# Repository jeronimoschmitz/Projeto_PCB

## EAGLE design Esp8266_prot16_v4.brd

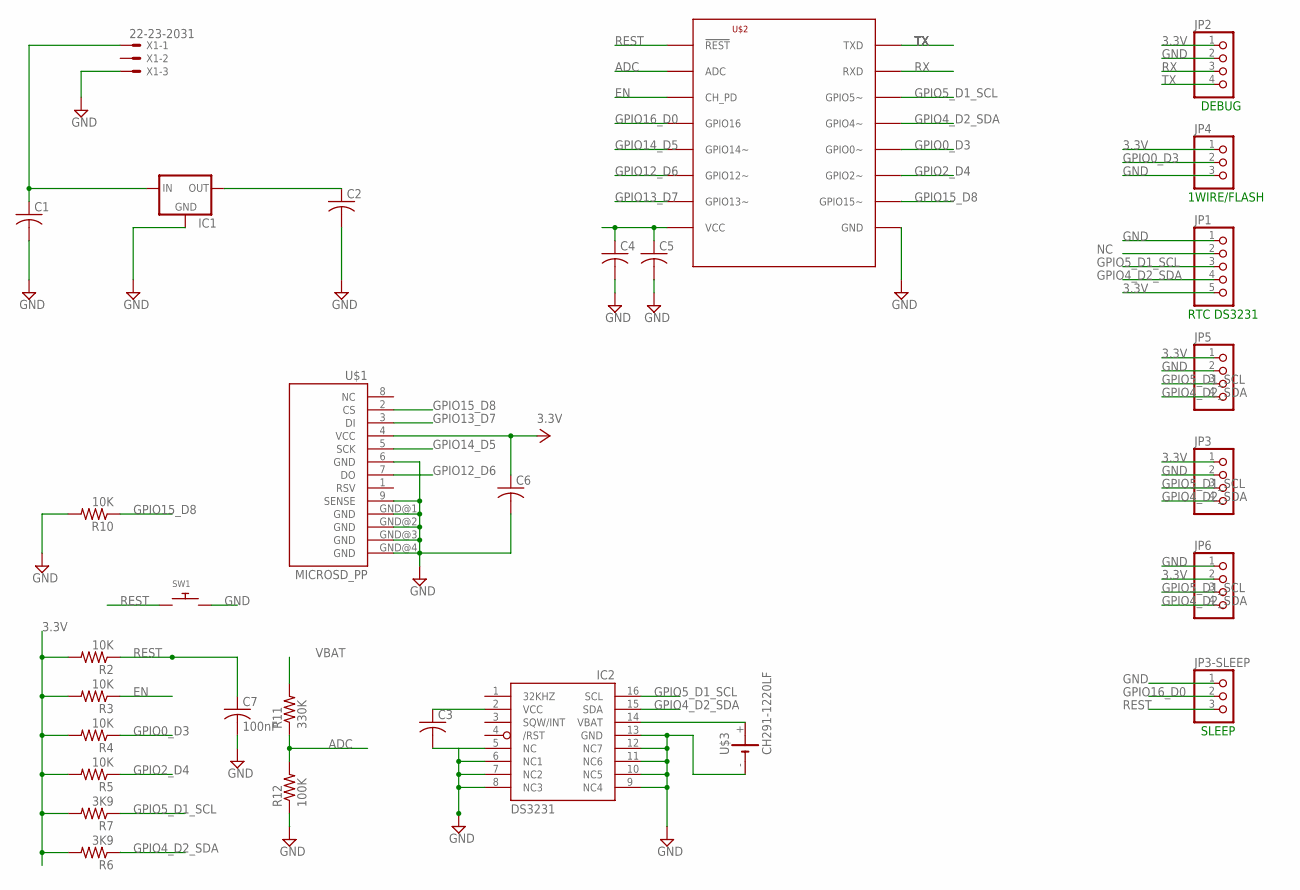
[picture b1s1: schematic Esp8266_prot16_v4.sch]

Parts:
C1, C2, C3, C4, C5, C6: C-USC0805K; C0805K
C7: 100nF; C0805K
IC1: XC63FPP; SOT89R
IC2: DS3231/SO; SO16W
JP1: PINHD-1X5/90; 1X05/90
JP2, JP5, JP6: PINHD-1X4; 1X04
JP3: PINHD-1X4/90; 1X04/90
JP3-SLEEP: PINHD-1X3/90; 1X03/90
JP4: PINHD-1X3; 1X03
R2, R3, R4, R5, R10: 10K; R0805
R6, R7: 3K9; R0805
R11: 330K; R0805
R12: 100K; R0805
SW1: SWITCH_PUSHBUTTONEVQ-PE; TACT_PANA-EVQ
U$1: MICROSD_PP
U$2: ESP8266-07; ESP-07
U$3: CH291-1220LF
X1: 22-23-2031

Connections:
3.3V: C2.1, C3.1, C4.1, C5.1, C6.1, IC1.3 (OUT), IC2.2 (VCC), JP1.5, JP2.1, JP3.1, JP4.1, JP5.1, JP6.2, R2.2, R3.2, R4.2, R5.2, R6.2, R7.2, U$1.4 (VCC), U$2.VCC
ADC: R11.1, R12.2, U$2.ADC
BATRTC: IC2.14 (VBAT), U$3.+
EN: R3.1, U$2.CH_PD
GND: C1.2, C2.2, C3.2, C4.2, C5.2, C6.2, C7.2, IC1.1 (GND), IC2.5 (NC), IC2.6 (NC1), IC2.7 (NC2), IC2.8 (NC3), IC2.9 (NC4), IC2.10 (NC5), IC2.11 (NC6), IC2.12 (NC7), IC2.13 (GND), JP1.1, JP2.2, JP3.2, JP3-SLEEP.1, JP4.3, JP5.2, JP6.1, R10.2, R12.1, SW1.P$2, U$1.6 (GND), U$1.9 (SENSE), U$1.GND@1 (GND), U$1.GND@2 (GND), U$1.GND@3 (GND), U$1.GND@4 (GND), U$2.GND, U$3.-, X1.3
GPIO0_D3: JP4.2, R4.1, U$2.GPIO0 (GPIO0~)
GPIO2_D4: R5.1, U$2.GPIO2 (GPIO2~)
GPIO4_D2_SDA: IC2.15 (SDA), JP1.4, JP3.4, JP5.4, JP6.4, R6.1, U$2.GPIO5 (GPIO4~)
GPIO5_D1_SCL: IC2.16 (SCL), JP1.3, JP3.3, JP5.3, JP6.3, R7.1, U$2.GPIO4 (GPIO5~)
GPIO12_D6: U$1.7 (DO), U$2.GPIO12 (GPIO12~)
GPIO13_D7: U$1.3 (DI), U$2.GPIO13 (GPIO13~)
GPIO14_D5: U$1.5 (SCK), U$2.GPIO14 (GPIO14~)
GPIO15_D8: R10.1, U$1.2 (CS), U$2.GPIO15 (GPIO15~)
GPIO16_D0: JP3-SLEEP.2, U$2.GPIO16
NC: JP1.2
REST: C7.1, JP3-SLEEP.3, R2.1, SW1.P$1, U$2.REST (!REST)
RX: JP2.3, U$2.RXD
TX: JP2.4, U$2.TXD
VBAT: C1.1, IC1.2 (IN), R11.2, X1.1

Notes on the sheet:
RTC DS3231
1WIRE/FLASH
DEBUG
SLEEP

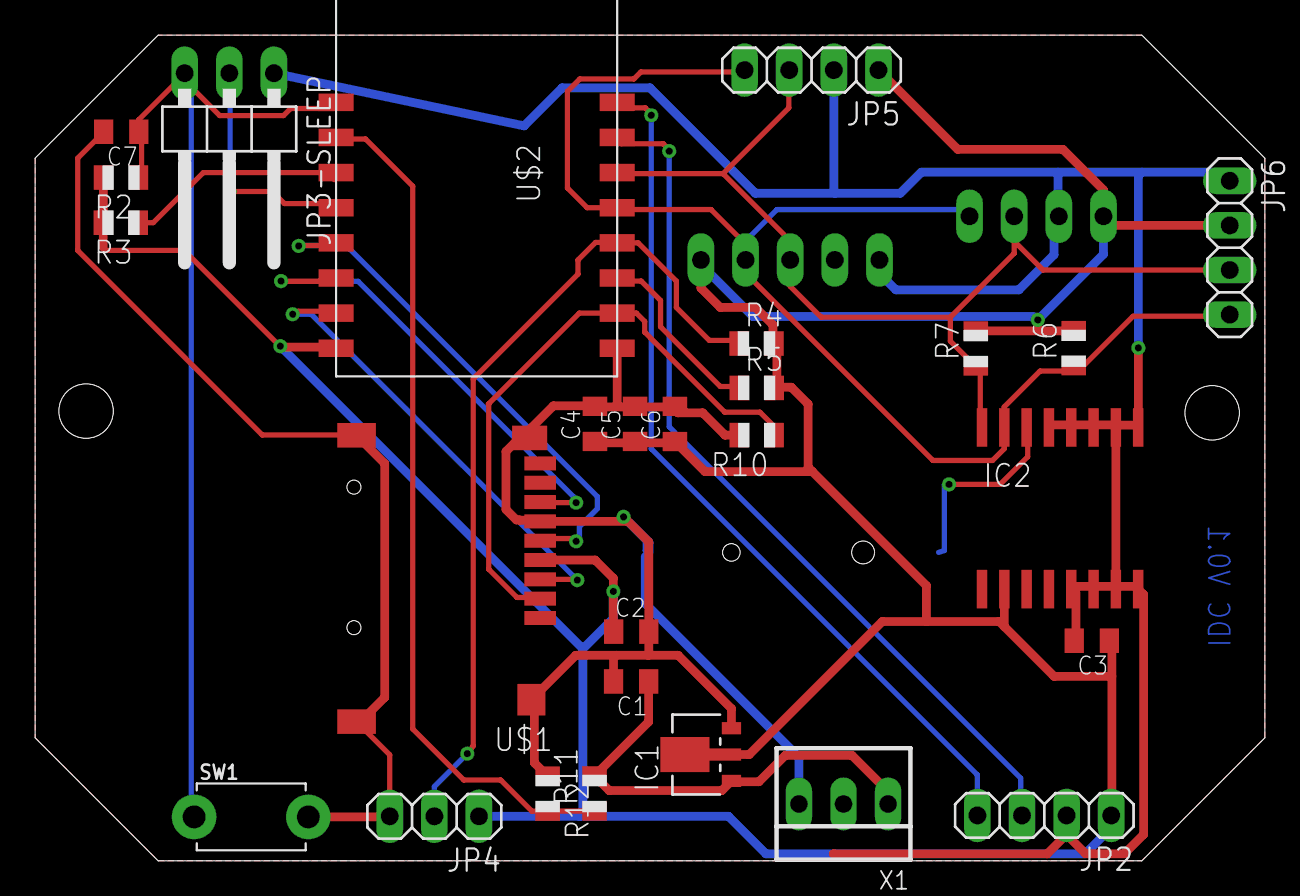
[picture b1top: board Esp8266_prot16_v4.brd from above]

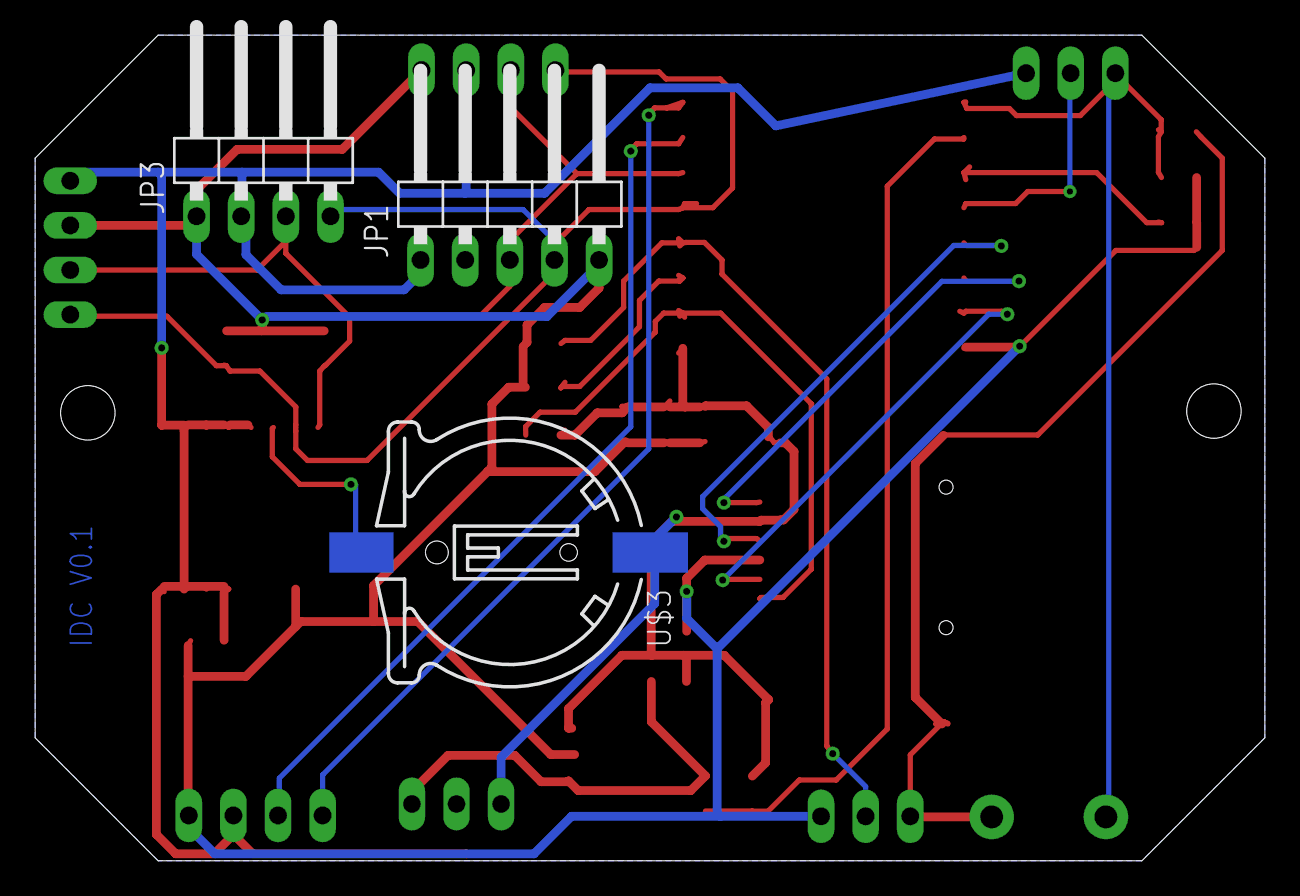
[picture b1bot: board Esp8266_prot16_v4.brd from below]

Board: 2 copper layers, 70.0 x 47.0 mm, 30 parts (3 on the bottom side), 18 nets.

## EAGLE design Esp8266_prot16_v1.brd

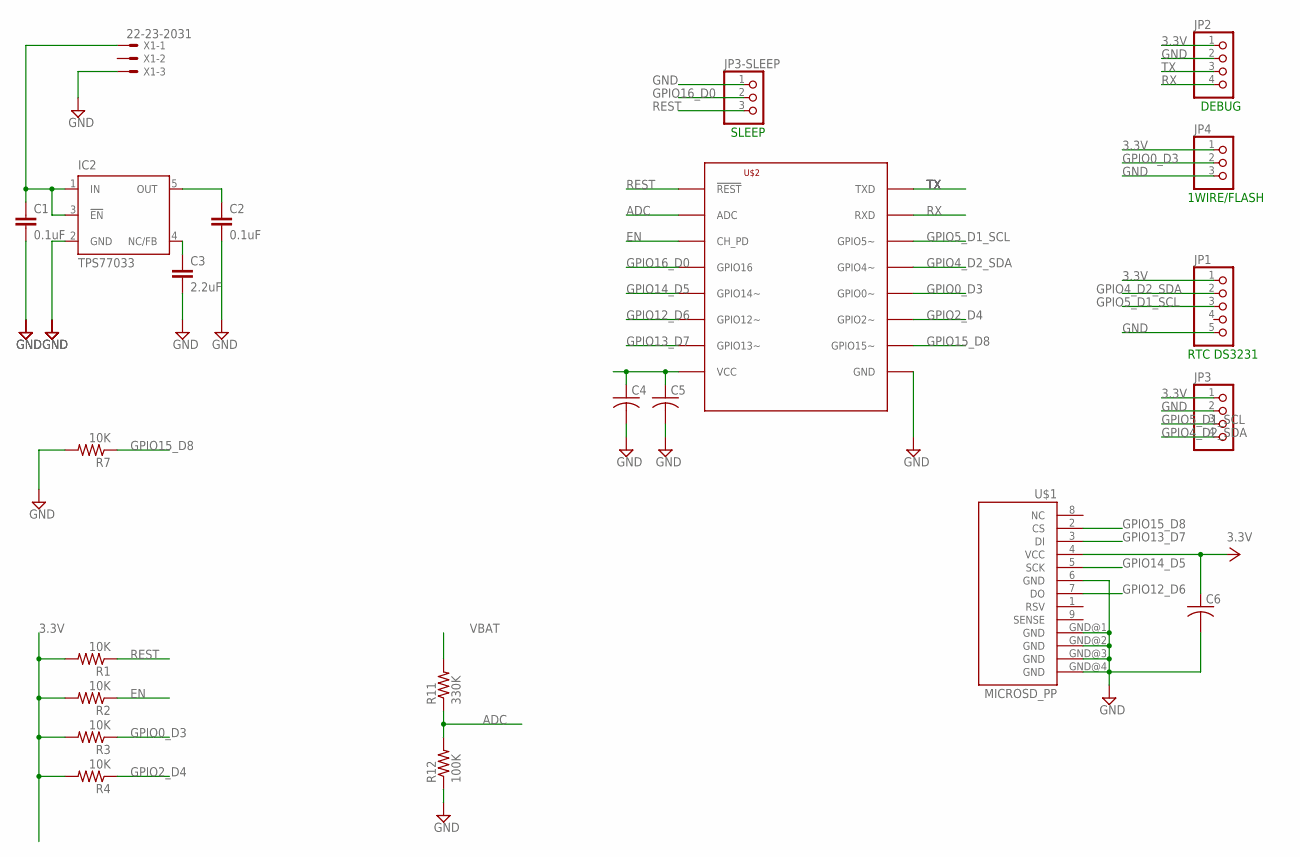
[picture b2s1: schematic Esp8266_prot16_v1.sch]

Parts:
C1, C2: 0.1uF; C0805
C3: 2.2uF; C0805
C4, C6: C-USC1206; C1206
C5: C-USC0805K; C0805K
IC2: TPS77033; SOT23-DBV; MPN TPS79301
JP1: PINHD-1X5; 1X05
JP2, JP3: PINHD-1X4; 1X04
JP3-SLEEP, JP4: PINHD-1X3; 1X03
R1, R2, R3: 10K; M0805
R4, R7: 10K; R0805
R11: 330K; R0805
R12: 100K; R0805
U$1: MICROSD_PP
U$2: ESP8266-07; ESP-07
X1: 22-23-2031

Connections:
3.3V: C2.1, C4.1, C5.1, C6.1, IC2.5 (OUT), JP1.1, JP2.1, JP3.1, JP4.1, R1.2, R2.2, R3.2, R4.2, U$1.4 (VCC), U$2.VCC
ADC: R11.1, R12.2, U$2.ADC
BYPASS: C3.1, IC2.4 (NC/FB)
EN: R2.1, U$2.CH_PD
GND: C1.2, C2.2, C3.2, C4.2, C5.2, C6.2, IC2.2 (GND), JP1.5, JP2.2, JP3.2, JP3-SLEEP.1, JP4.3, R7.2, R12.1, U$1.6 (GND), U$1.GND@1 (GND), U$1.GND@2 (GND), U$1.GND@3 (GND), U$1.GND@4 (GND), U$2.GND, X1.3
GPIO0_D3: JP4.2, R3.1, U$2.GPIO0 (GPIO0~)
GPIO2_D4: R4.1, U$2.GPIO2 (GPIO2~)
GPIO4_D2_SDA: JP1.2, JP3.4, U$2.GPIO5 (GPIO4~)
GPIO5_D1_SCL: JP1.3, JP3.3, U$2.GPIO4 (GPIO5~)
GPIO12_D6: U$1.7 (DO), U$2.GPIO12 (GPIO12~)
GPIO13_D7: U$1.3 (DI), U$2.GPIO13 (GPIO13~)
GPIO14_D5: U$1.5 (SCK), U$2.GPIO14 (GPIO14~)
GPIO15_D8: R7.1, U$1.2 (CS), U$2.GPIO15 (GPIO15~)
GPIO16_D0: JP3-SLEEP.2, U$2.GPIO16
REST: JP3-SLEEP.3, R1.1, U$2.REST (!REST)
RX: JP2.4, U$2.RXD
TX: JP2.3, U$2.TXD
VBAT: C1.1, IC2.1 (IN), IC2.3 (!EN), R11.2, X1.1

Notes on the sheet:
RTC DS3231
1WIRE/FLASH
DEBUG
SLEEP

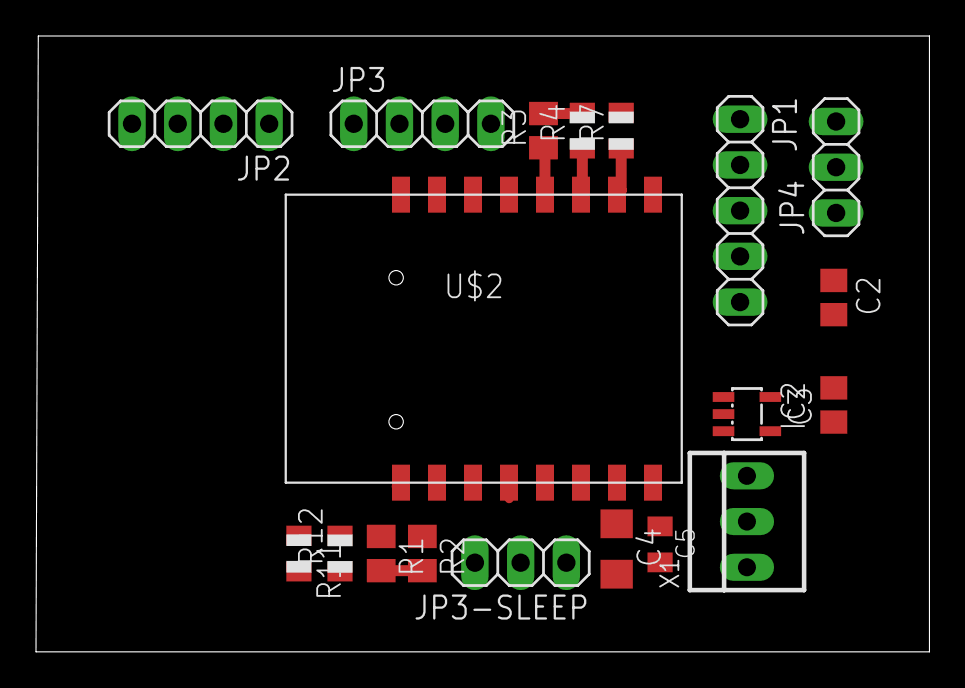
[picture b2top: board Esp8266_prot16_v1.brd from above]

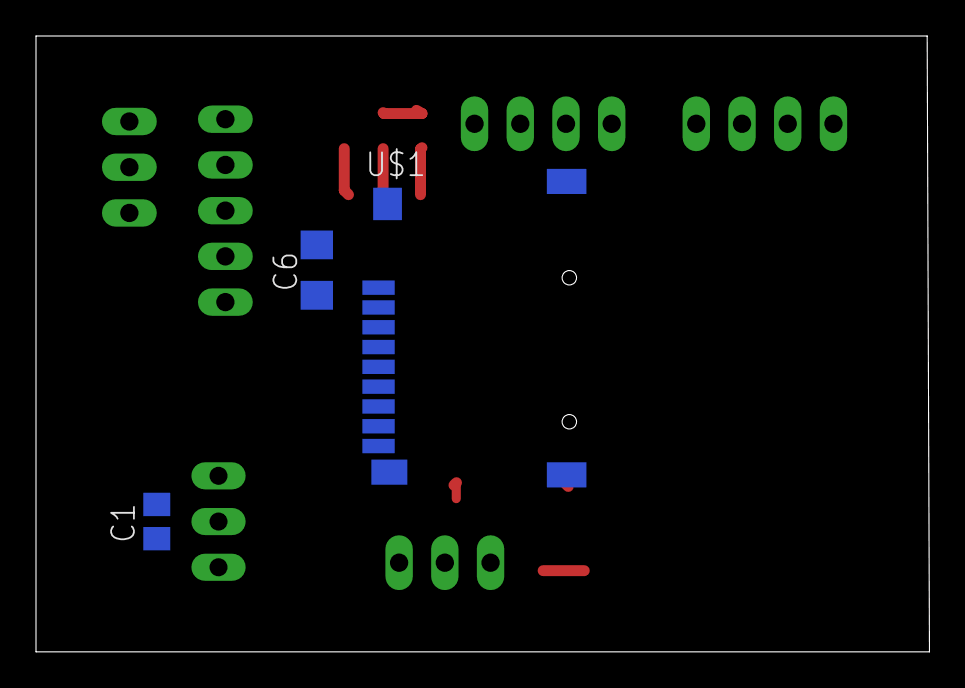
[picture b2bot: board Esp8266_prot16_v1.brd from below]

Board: 2 copper layers, 49.6 x 34.2 mm, 22 parts (3 on the bottom side), 18 nets.

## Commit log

2017-11-07 Projeto inicial PCB
2017-12-12 Inicio Repositorio
